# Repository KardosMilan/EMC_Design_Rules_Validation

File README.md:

# Automotive SEPIC Converter — EMC Design Rules Validation

> **Complete engineering workflow for an automotive-grade SEPIC DC-DC converter, from power-stage dimensioning through iterative EMC filter development to laboratory validation.**

---

## Overview

This project documents the full development and validation cycle of a switching power supply designed to meet demanding automotive EMC requirements. Starting from topology selection and component dimensioning, the work progresses through multiple hardware revisions, EMC-oriented filter design, and systematic laboratory validation — including electrical, frequency-domain, and thermal measurements.

Two contrasting PCB design iterations (SEPIC-A2 and SEPIC-B) are included side by side, demonstrating the measurable EMC impact of layout and filter decisions.

## Example of a designed PCB in aluminium housing

---

## Project Goals

- Design an automotive SEPIC converter power stage with appropriate switching-frequency selection and thermal management
- Identify and characterise conducted and radiated emission sources
- Develop and iteratively optimise LC input/output EMC filters
- Validate all design decisions through laboratory measurements
- Correlate theoretical calculations with experimental results
- Produce a documented engineering process suitable for future design iterations

---

## Engineering Workflow

### 1 — System Design
Component selection, power-stage dimensioning, switching-frequency optimisation, thermal considerations, and initial PCB layout preparation.

### 2 — EMC Filter Development
LC filter calculations, topology comparison, resonance analysis, and iterative optimisation verified against laboratory measurements. All calculation sheets are included in the repository.

### 3 — Prototype Manufacturing
Custom PCB design with microcontroller integration, automotive-grade components, and dedicated measurement interfaces. Two hardware revisions are provided:

| Revision     | Design Intent                                                        |
|---|---|
| **SEPIC-A2** | Reference iteration — poor EMC layout (emission source example)      |
| **SEPIC-B**  | Optimised iteration — improved EMC layout and filter (target design) |

### 4 — Measurement & Validation

| Domain      | Method                                                                               |
|---|---|
| Electrical  | Switching waveform analysis, frequency-domain characterisation, noise quantification |
| EMC         | Conducted emission measurement, filter effectiveness comparison between revisions    |
| Thermal     | FLIR thermal imaging, hotspot identification, thermal performance validation         |
| Correlation | Calculated vs. measured comparison across all key parameters                         |

---

## Repository Structure

```
EMC_Design_Rules_Validation/
├── 01_Documents/
│   ├── Filter design documentation
│   ├── Measurement plans
│   ├── Correlation calculations
│   ├── Thermal analysis results
│   └── Oscilloscope captures
│
├── 02_Pictures/
│   ├── Prototype photos
│   └── Laboratory setup
│
├── 03_Calculations/
│   ├── Design calculations
│   ├── EMC filter calculations
│   └── Validation worksheets
│
├── 04_SEPIC_microcontroller_prototype/
│   ├── Prototype hardware
│   ├── Embedded controller integration
│   └── Supporting component libraries
│
└── 05_HW_design/
    ├── SEPIC-A2/     ← bad EMC design example
    ├── SEPIC-B/      ← optimised EMC design example
    └── PCB design resources
```

---

## Technology Stack

| Area                   | Tools & Methods                         |
|---|---|
| PCB Design             | CAD schematic & layout tools            |
| Calculations           | Excel-based engineering worksheets      |
| Electrical Measurement | Oscilloscope (time & frequency domain)  |
| Thermal Measurement    | FLIR thermal camera                     |
| EMC Measurement        | Conducted emission laboratory equipment |
| Embedded Platform      | Automotive-grade microcontroller        |

---

## Key Outcomes

- Designed and validated two SEPIC converter hardware revisions with measurably different EMC behaviour
- Developed EMC filter solutions grounded in both analytical calculation and experimental iteration
- Demonstrated a systematic correlation methodology between design predictions and laboratory results
- Produced a complete, reproducible engineering workflow applicable to future power electronics and EMC projects

---

## Author

**Kardos Milan**  
Electrical / Electronics Engineer  
*Specialising in Power Electronics, EMC Validation, Hardware Design, and Embedded Systems*

---

## License

This repository is shared for portfolio and reference purposes. All rights reserved.

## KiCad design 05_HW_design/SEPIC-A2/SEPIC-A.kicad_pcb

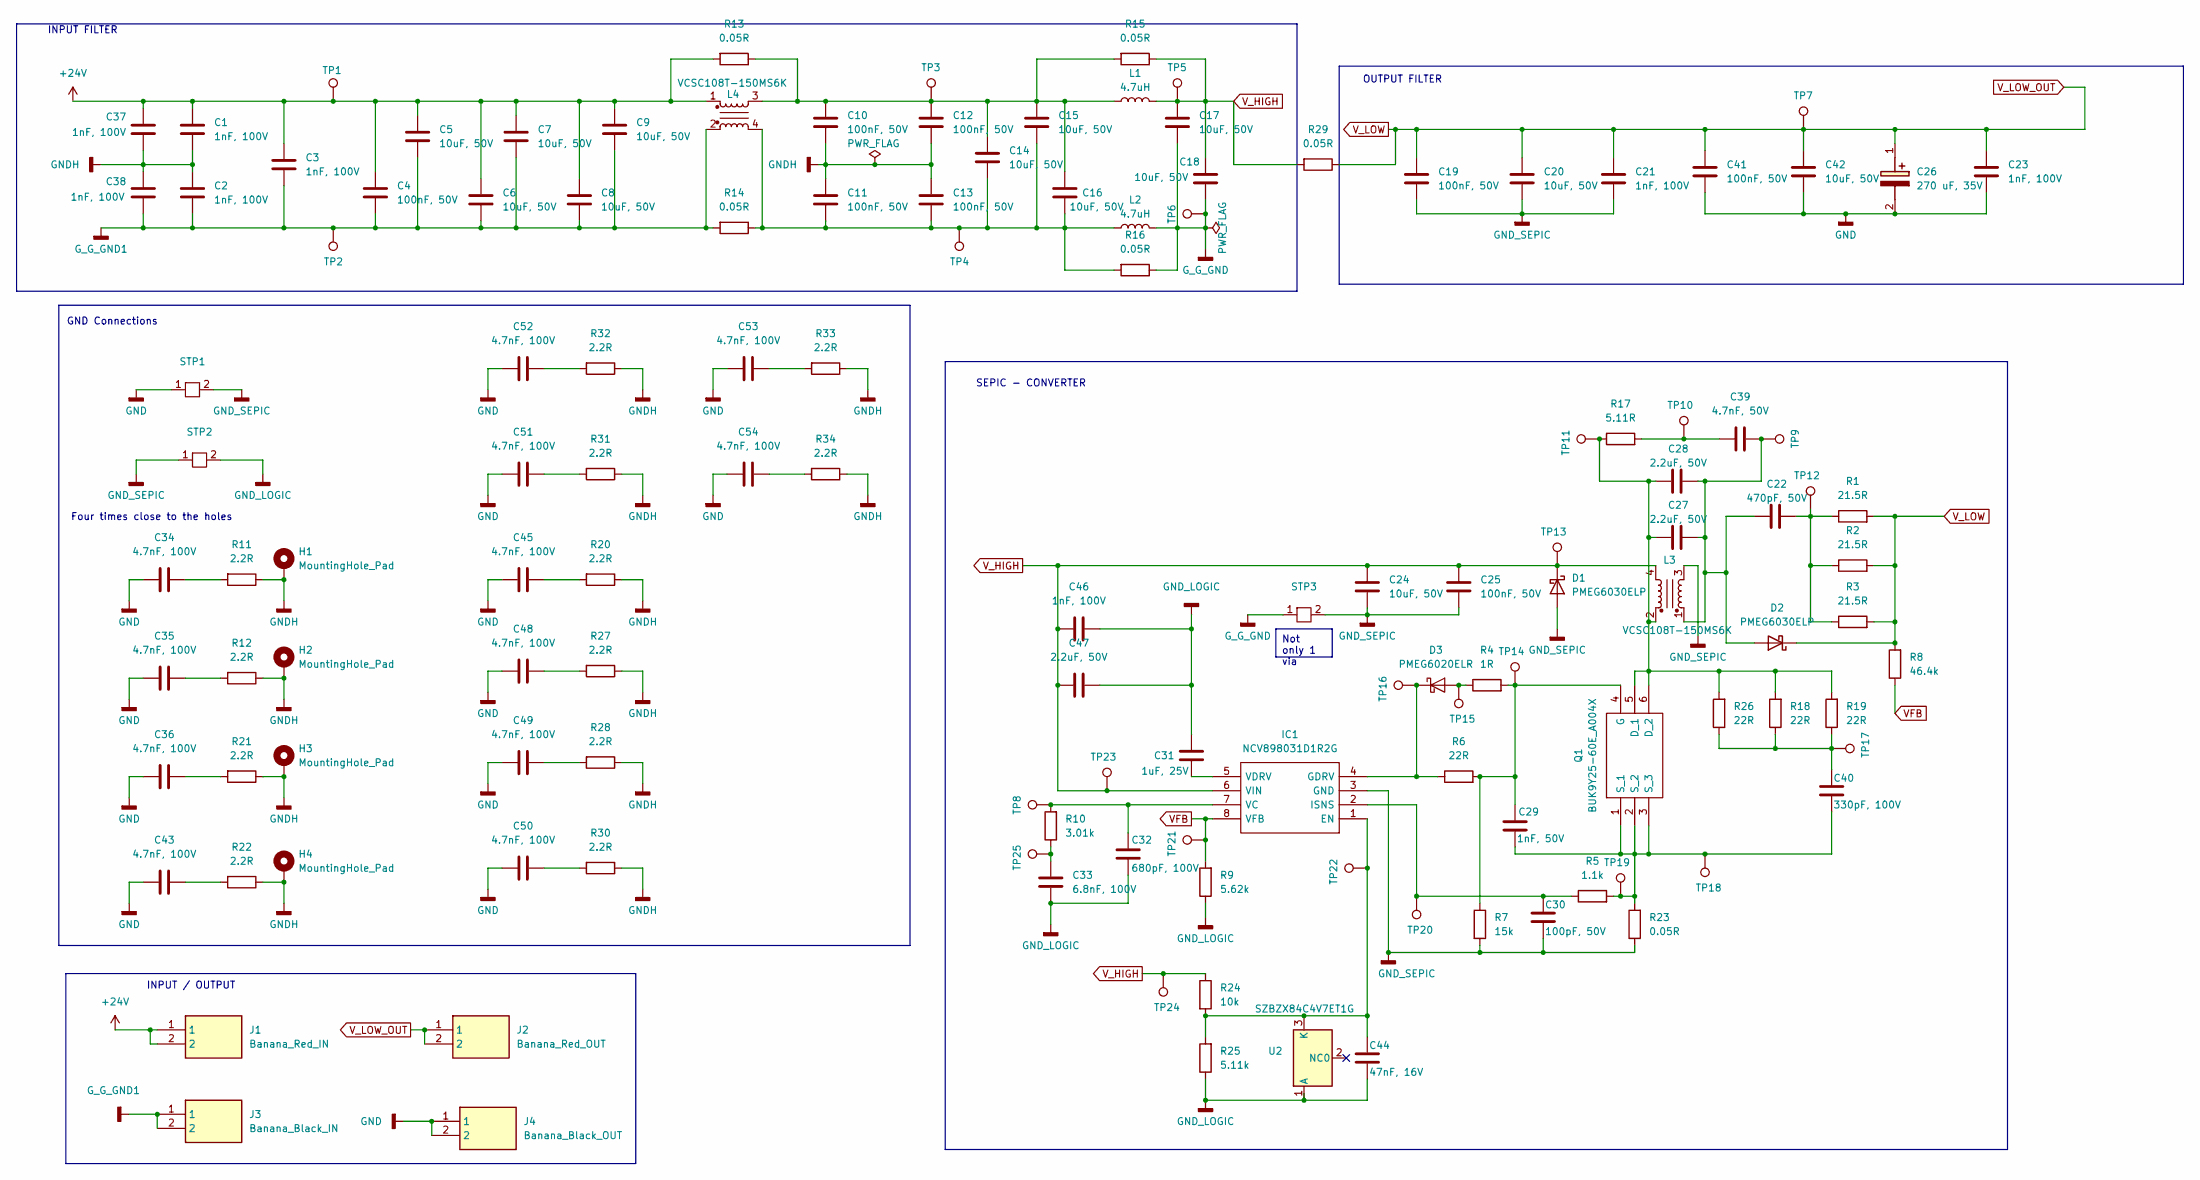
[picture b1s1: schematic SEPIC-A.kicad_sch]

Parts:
C1, C2, C3, C21, C23, C37, C38, C46: 1nF, 100V; C_0805_2012Metric_Pad1.18x1.45mm_HandSolder
C4, C10, C11, C12, C13, C19, C25, C41: 100nF, 50V; C_0805_2012Metric_Pad1.18x1.45mm_HandSolder
C5, C6, C7, C8, C9, C14, C15, C16, C17, C18, C20, C24, C42: 10uF, 50V; C_1210_3225Metric_Pad1.33x2.70mm_HandSolder
C22: 470pF, 50V; C_0603_1608Metric_Pad1.08x0.95mm_HandSolder
C26: 270 uF, 35V; CP_Elec_10x10.5; Manufacturer_Part_Number B40900B7277M000
C27, C28, C47: 2.2uF, 50V; C_1206_3216Metric_Pad1.33x1.80mm_HandSolder
C29: 1nF, 50V; C_0402_1005Metric
C30: 100pF, 50V; C_0402_1005Metric_Pad0.74x0.62mm_HandSolder
C31: 1uF, 25V; C_0805_2012Metric_Pad1.18x1.45mm_HandSolder
C32: 680pF, 100V; C_0603_1608Metric_Pad1.08x0.95mm_HandSolder
C33: 6.8nF, 100V; C_0603_1608Metric_Pad1.08x0.95mm_HandSolder
C34, C35, C36, C43, C45, C48, C49, C50, C51, C52, C53, C54: 4.7nF, 100V; C_0805_2012Metric_Pad1.18x1.45mm_HandSolder
C39: 4.7nF, 50V; C_1206_3216Metric_Pad1.33x1.80mm_HandSolder
C40: 330pF, 100V; C_0402_1005Metric_Pad0.74x0.62mm_HandSolder
C44: 47nF, 16V; C_0402_1005Metric_Pad0.74x0.62mm_HandSolder
D1, D2: PMEG6030ELP; D_SOD-128
D3: PMEG6020ELR; Nexperia_CFP3_SOD-123W
H1, H2, H3, H4: MountingHole_Pad; MountingHole_3.2mm_M3_Pad_Via
IC1: NCV898031D1R2G; SOIC127P600X175-8N; Manufacturer_Part_Number NCV898031D1R2G
J1: Banana_Red_IN; 242431; Manufacturer_Part_Number 24.243.1
J2: Banana_Red_OUT; 242431; Manufacturer_Part_Number 24.243.1
J3: Banana_Black_IN; 242432; Manufacturer_Part_Number 24.243.2
J4: Banana_Black_OUT; 242432; Manufacturer_Part_Number 24.243.2
L1, L2: 4.7uH; CLF6045__
L3, L4: VCSC108T-150MS6K; VCSC108T
Q1: BUK9Y25-60E_A004X; BUK9Y2560EA004X; Manufacturer_Part_Number BUK9Y25-60E/A004X
R1, R2, R3: 21.5R; R_0805_2012Metric_Pad1.20x1.40mm_HandSolder
R4: 1R; R_0805_2012Metric_Pad1.20x1.40mm_HandSolder
R5: 1.1k; R_0805_2012Metric_Pad1.20x1.40mm_HandSolder
R6, R18, R19, R26: 22R; R_0805_2012Metric_Pad1.20x1.40mm_HandSolder
R7: 15k; R_0402_1005Metric_Pad0.72x0.64mm_HandSolder
R8: 46.4k; R_0805_2012Metric_Pad1.20x1.40mm_HandSolder
R9: 5.62k; R_0402_1005Metric_Pad0.72x0.64mm_HandSolder
R10: 3.01k; R_0402_1005Metric_Pad0.72x0.64mm_HandSolder
R11, R12, R20, R21, R22, R27, R28, R30, R31, R32, R33, R34: 2.2R; R_0603_1608Metric_Pad0.98x0.95mm_HandSolder
R13, R14, R15, R16, R29: 0.05R; R_0805_2012Metric_Pad1.20x1.40mm_HandSolder
R17: 5.11R; C_0805_2012Metric_Pad1.18x1.45mm_HandSolder
R23: 0.05R; R_2512_6332Metric_Pad1.40x3.35mm_HandSolder
R24: 10k; R_0805_2012Metric_Pad1.20x1.40mm_HandSolder
R25: 5.11k; R_0805_2012Metric_Pad1.20x1.40mm_HandSolder
STP1, STP2, STP3: STP
TP1, TP2, TP3, TP4, TP5, TP6, TP7, TP8, TP9, TP10, TP11, TP12, TP13, TP14, TP15, TP16, TP17, TP18, TP19, TP20, TP21, TP22, TP23, TP24, TP25: TestPoint; TestPoint_Pad_D1.1mm
U2: SZBZX84C4V7ET1G; SOT-23

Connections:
+24V: C1.1, C3.1, C4.1, C5.1, C6.1, C7.1, C8.1, C9.1, C37.1, J1.1, J1.2, L4.1, R13.2, TP1.1
GND: C23.2, C26.2 (-), C34.1, C35.1, C36.1, C41.2, C42.2, C43.1, C45.1, C48.1, C49.1, C50.1, C51.1, C52.1, C53.1, C54.1, J4.1, J4.2, STP1.1
GNDH: C1.2, C2.1, C10.2, C11.1, C12.2, C13.1, C37.2, C38.1, H1.1, H2.1, H3.1, H4.1, R11.1, R12.1, R20.1, R21.1, R22.1, R27.1, R28.1, R30.1, R31.1, R32.1, R33.1, R34.1
GND_LOGIC: C31.1, C32.2, C33.2, C44.2, C46.2, C47.2, R9.1, R25.1, STP2.2, U2.1 (A)
GND_SEPIC: C19.2, C20.2, C21.2, C24.2, C25.2, C30.2, D1.2 (A), IC1.3 (GND), L3.3, R7.2, R23.1, STP1.2, STP2.1, STP3.2
G_G_GND: C17.2, C18.2, L2.2, R16.1, STP3.1, TP6.1
G_G_GND1: C2.2, C3.2, C4.2, C5.2, C6.2, C7.2, C8.2, C9.2, C38.2, J3.1, J3.2, L4.2, R14.2, TP2.1
unnamed: C10.1, C12.1, C14.1, C15.1, C16.1, L1.1, L4.3, R13.1, R15.2, TP3.1
unnamed: C11.2, C13.2, C14.2, C15.2, C16.2, L2.1, L4.4, R14.1, R16.2, TP4.1
unnamed: C22.2, R1.1, R2.1, R3.1, TP12.1
unnamed: C33.1, R10.1, TP25.1
unnamed: C34.2, R11.2
unnamed: C35.2, R12.2
unnamed: C36.2, R21.2
unnamed: C39.1, R17.2, TP10.1
unnamed: C40.1, R18.1, R19.1, R26.1, TP17.1
unnamed: C43.2, R22.2
unnamed: C45.2, R20.2
unnamed: C48.2, R27.2
unnamed: C49.2, R28.2
unnamed: C50.2, R30.2
unnamed: C51.2, R31.2
unnamed: C52.2, R32.2
unnamed: C53.2, R33.2
unnamed: C54.2, R34.2
unnamed: C22.1, C27.2, C28.2, C39.2, D2.2 (A), L3.1, TP9.1
unnamed: D3.2 (A), R4.1, TP15.1
unnamed: D3.1 (K), IC1.4 (GDRV), R6.1, TP16.1
unnamed: C44.1, IC1.1 (EN), R24.2, R25.2, TP22.1, U2.3 (K)
unnamed: C30.1, IC1.2 (ISNS), R5.1, TP20.1
unnamed: C32.1, IC1.7 (VC), R10.2, TP8.1
unnamed: C31.2, IC1.5 (VDRV)
unnamed: C27.1, C28.1, L3.2, Q1.5 (D_1), Q1.6 (D_2), R17.1, R18.2, R19.2, R26.2, TP11.1
unnamed: C29.1, Q1.4 (G), R4.2, R6.2, R7.1, TP14.1
unnamed: C29.2, C40.2, Q1.1 (S_1), Q1.2 (S_2), Q1.3 (S_3), R5.2, R23.2, TP18.1, TP19.1
VFB: IC1.8 (VFB), R8.1, R9.2, TP21.1
V_HIGH: C17.1, C18.1, C24.1, C25.1, C46.1, C47.1, D1.1 (K), IC1.6 (VIN), L1.2, L3.4, R15.1, R24.1, R29.2, TP5.1, TP13.1, TP23.1, TP24.1
V_LOW: C19.1, C20.1, C21.1, C23.1, C26.1 (+), C41.1, C42.1, D2.1 (K), J2.1, J2.2, R1.2, R2.2, R3.2, R8.2, R29.1, TP7.1

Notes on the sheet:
Not only 1 via
SEPIC - CONVERTER
GND Connections
INPUT FILTER
Four times close to the holes
INPUT / OUTPUT
OUTPUT FILTER

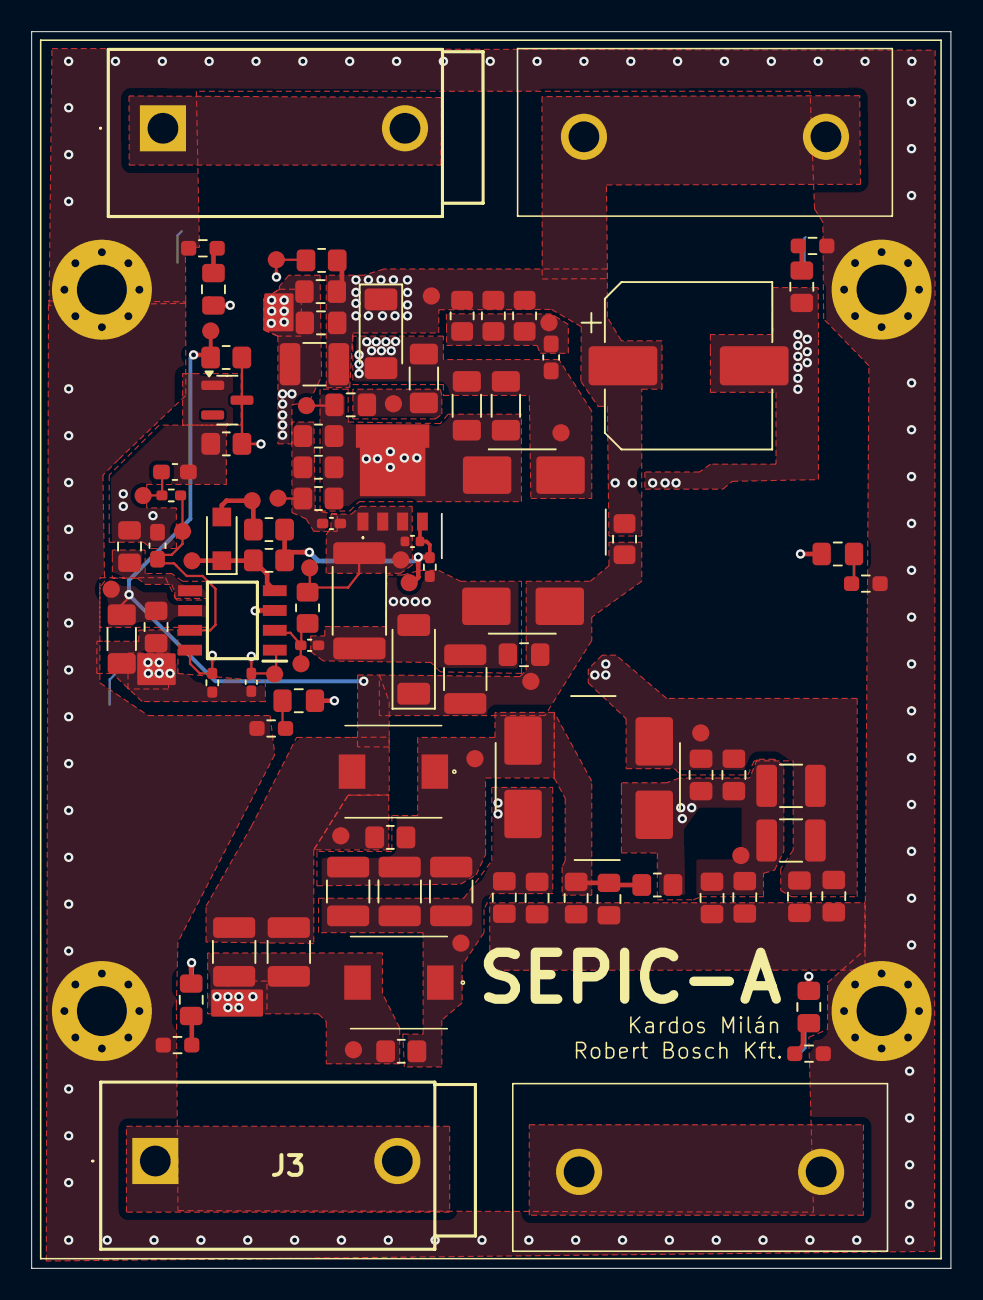
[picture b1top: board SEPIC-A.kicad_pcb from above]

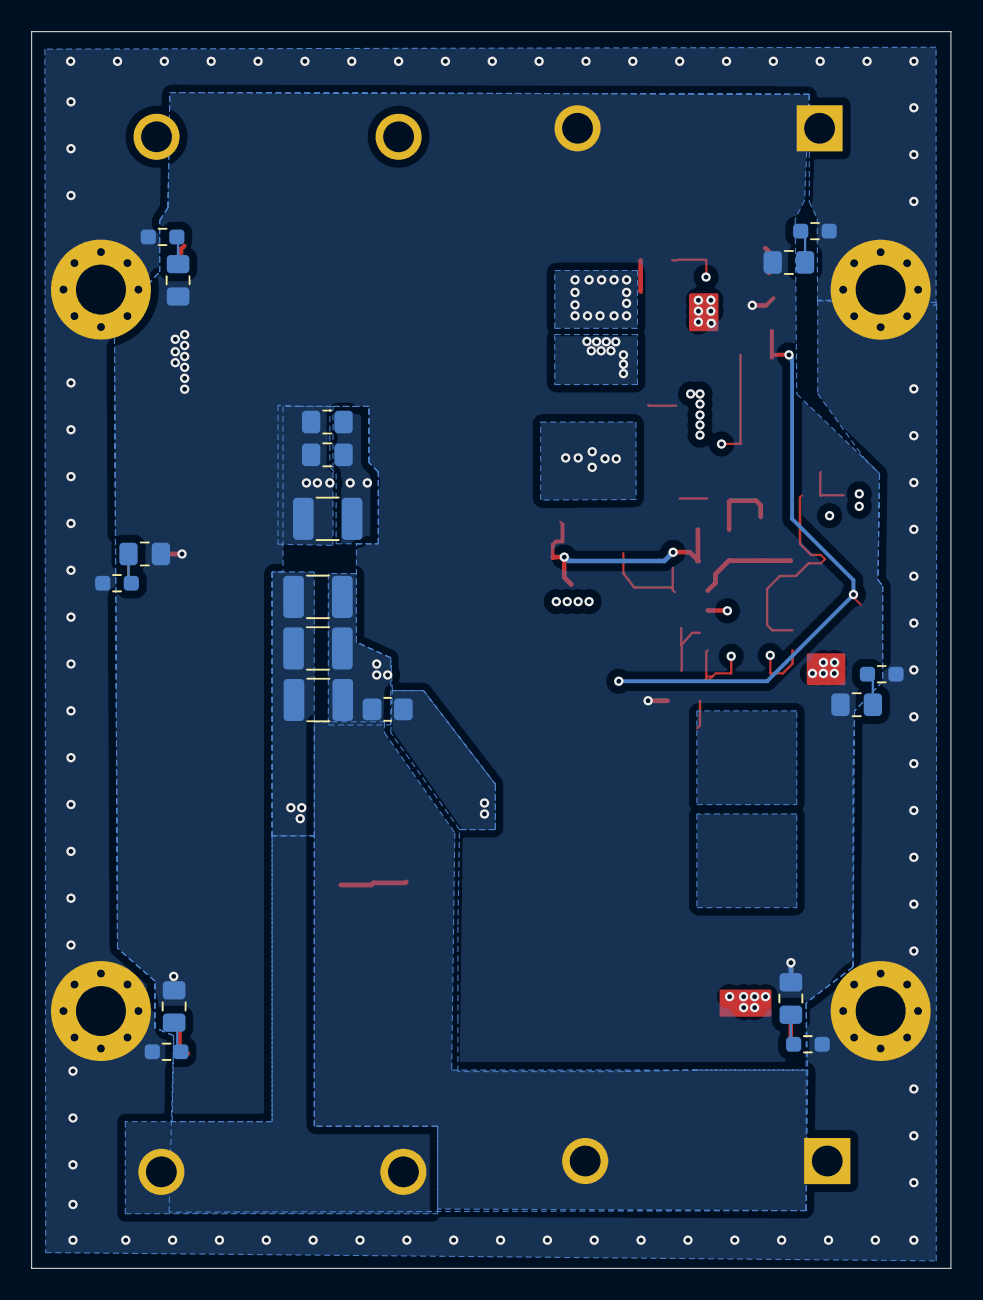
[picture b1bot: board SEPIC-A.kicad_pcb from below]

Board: 6 copper layers, 58.9 x 79.2 mm, 134 parts (19 on the bottom side), 38 nets.

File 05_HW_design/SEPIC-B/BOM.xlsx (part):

Reference | Value | Shop | Datasheet | Footprint | Qty | Bolti Darab | Ár (ft) | Összesen |  | 4db PCB-re [db] | Összesen [ft]
R5 | 1.1k | https://hu.farnell.com/panasonic/erj6geyj112v/res-1k1-5-0-12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 | http://industrial.panasonic.com/cdbs/www-data/pdf/RDA0000/AO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 | Resistor_SMD:R_0805_2012Metric_Pad1.20x1.40mm_HandSolder | 1 | 10 | 14.7 | 147 |  | 4 | 147
R4 | 1R | https://hu.farnell.com/bourns/cr0805-j-1r0elf/res-1r-5-0-125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 | https://www.farnell.com/datasheets/3693949.pdf | Resistor_SMD:R_0805_2012Metric_Pad1.20x1.40mm_HandSolder | 1 | 10 | 3.6 | 36 |  | 4 | 36
R28 | R | https://hu.farnell.com/walsin/wr12x151-jtl/res-150r-5-0-25w-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 | https://4donline.ihs.com/images/VipMasterIC/IC/WATC/WATC-S-A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 | Resistor_SMD:R_1206_3216Metric_Pad1.30x1.75mm_HandSolder | 1 | 10 | 5.5709999999999997 | 55.71 |  | 4 | 55.71
C31 | 1uF, 25V | https://hu.farnell.com/avx/08053g105zat2a/cap-1-f-25v-y5v-08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 | https://4donline.ihs.com/images/VipMasterIC/IC/AVXC/AVXC-S-A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 | Capacitor_SMD:C_0805_2012Metric_Pad1.18x1.45mm_HandSolder | 1 | 10 | 42.88 | 428.8 |  | 4 | 428.8
C32 | 680pF, 100V | https://hu.farnell.com/avx/06031c681kat2a/cap-680pf-100v-mlc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 | https://4donline.ihs.com/images/VipMasterIC/IC/AVXC/AVXC-S-A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 | Capacitor_SMD:C_0603_1608Metric_Pad1.08x0.95mm_HandSolder | 1 | 10 | 18 | 180 |  | 4 | 180
C5,C6,C7,C8,C9,C14,C15,C16,C17,C18,C20,C42 | 10uF, 50V | https://hu.farnell.com/tdk/cga6p3x7s1h106k250ab/cap-10-f-50v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 | https://www.farnell.com/datasheets/3816851.pdf | Capacitor_SMD:C_1210_3225Metric_Pad1.33x2.70mm_HandSolder | 12 | 12 | 244.47 | 2933.64 |  | 48 | 11734.56
C4,C10,C11,C12,C13,C19,C41 | 100nF, 50V | https://hu.farnell.com/kemet/c0805x104j5rac3316/cap-0-1-f-50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 | https://4donline.ihs.com/images/VipMasterIC/IC/KEME/KEME-S-A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 | Capacitor_SMD:C_0805_2012Metric_Pad1.18x1.45mm_HandSolder | 7 | 10 | 293 | 2930 |  | 28 | 8204
C1,C2,C3,C21,C23,C37,C38,C46 | 1nF, 100V | https://hu.farnell.com/kemet/c0805x102k1racauto/cap-1000pf-1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 | https://4donline.ihs.com/images/VipMasterIC/IC/KEME/KEME-S-A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 | Capacitor_SMD:C_0805_2012Metric_Pad1.18x1.45mm_HandSolder | 8 | 10 | 84 | 840 |  | 32 | 2688
C47 | 2.2uF, 50V | https://hu.farnell.com/kemet/c1206c225m5ractu/cap-2-2-f-50v-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 | https://search.kemet.com/component-documentation/download/sp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 | Capacitor_SMD:C_1206_3216Metric_Pad1.33x1.80mm_HandSolder | 1 | 10 | 89 | 890 |  | 4 | 890
C22 | 470pF, 50V | https://hu.farnell.com/kemet/c0603s471k5racauto/cap-mlcc-aec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 | https://4donline.ihs.com/images/VipMasterIC/IC/KEME/KEME-S-A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 | Capacitor_SMD:C_0603_1608Metric_Pad1.08x0.95mm_HandSolder | 1 | 10 | 75 | 750 |  | 4 | 750
C30 | 100pF, 50V | https://hu.farnell.com/kemet/c0402c101k5gacauto/cap-100pf-50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 | https://4donline.ihs.com/images/VipMasterIC/IC/KEME/KEME-S-A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 | Capacitor_SMD:C_0402_1005Metric_Pad0.74x0.62mm_HandSolder | 1 | 10 | 14 | 140 |  | 4 | 140
C29 | 1nF, 50V | https://hu.farnell.com/kemet/c0402c102j5racauto/cap-1000pf-5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 | https://4donline.ihs.com/images/VipMasterIC/IC/KEME/KEME-S-A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 | Capacitor_SMD:C_0402_1005Metric | 1 | 10 | 16 | 160 |  | 4 | 160
C34,C35,C36,C43 | 4.7nF, 100V | https://hu.farnell.com/kemet/c0805c472k1ractu/cap-4700pf-100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 | https://4donline.ihs.com/images/VipMasterIC/IC/KEME/KEME-S-A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 | Capacitor_SMD:C_0805_2012Metric_Pad1.18x1.45mm_HandSolder | 4 | 10 | 57 | 570 |  | 16 | 912
D1,D2 | PMEG6030ELP | https://hu.farnell.com/nexperia/pmeg6030elpx/schottky-rect-3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 | https://4donline.ihs.com/images/VipMasterIC/IC/NEXP/NEXP-S-A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 | Diode_SMD:D_SOD-128 | 2 | 5 | 192 | 960 |  | 8 | 1536
U2 | SZBZX84C4V7ET1G | https://hu.farnell.com/on-semiconductor/szbzx84c4v7et1g/zene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 | https://4donline.ihs.com/images/VipMasterIC/IC/ONSM/ONSM-S-A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 | Package_TO_SOT_SMD:SOT-23 | 1 | 5 | 98.5 | 492.5 |  | 4 | 492.5
R9 | 5.62k | https://hu.farnell.com/panasonic/erj2rkf5621x/res-5k62-1-0-1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 | https://4donline.ihs.com/images/VipMasterIC/IC/PANA/PANA-S-A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 | Resistor_SMD:R_0402_1005Metric_Pad0.72x0.64mm_HandSolder | 1 | 10 | 10.5 | 105 |  | 4 | 105
R6,R18,R19,R26 | 22R | https://hu.farnell.com/multicomp-pro/mp000064/res-aec-q200-2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 | https://4donline.ihs.com/images/VipMasterIC/IC/SCMP/SCMP-S-A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 | Resistor_SMD:R_0805_2012Metric_Pad1.20x1.40mm_HandSolder | 4 | 10 | 23.44 | 234.4 |  | 16 | 375.04
R23 | 0.05R | https://hu.farnell.com/multicomp-pro/mclrp12jtdrr050/res-det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 | https://4donline.ihs.com/images/VipMasterIC/IC/SCMP/SCMP-S-A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 | Resistor_SMD:R_2512_6332Metric_Pad1.40x3.35mm_HandSolder | 6 | 10 | 133.4 | 1334 |  | 24 | 3201.6
Q1 | BUK9Y25-60E_A004X | https://hu.farnell.com/nexperia/buk9y25-60e-115/mosfet-aecq1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 | https://assets.nexperia.com/documents/data-sheet/BUK9Y25-60E.pdf | KiCad1:BUK9Y2560EA004X | 1 | 1 | 345 | 345 |  | 4 | 1380
D3 | PMEG6020ELR | https://hu.farnell.com/nexperia/pmeg6020elrx/rectifier-schot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 | https://assets.nexperia.com/documents/data-sheet/PMEG6020ELR.pdf | Diode_SMD:Nexperia_CFP3_SOD-123W | 1 | 5 | 187.9 | 939.5 |  | 4 | 939.5
C26 | 270 uF, 35V | https://at.farnell.com/en-AT/epcos/b40900b7277m000/cap-270uf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 | https://product.tdk.com/system/files/dam/doc/product/capacit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 | Capacitor_SMD:CP_Elec_10x10.5 | 1 | Itthon nem elérhet? csak 1000 darabos |  |  | euroban lehet csak | 4
C40 | 330pF, 100V | https://hu.farnell.com/kemet/c0402c331j1gactu/cap-330pf-100v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 | https://search.kemet.com/component-documentation/download/sp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 | Capacitor_SMD:C_0402_1005Metric_Pad0.74x0.62mm_HandSolder | 1 | 10 | 29.3 | 293 |  | 4 | 293
C44 | 47nF, 16V | https://hu.farnell.com/yageo/cc0402krx7r7bb472/cap-4700pf-16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 | https://www.yageo.com/upload/media/product/productsearch/dat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 | Capacitor_SMD:C_0402_1005Metric_Pad0.74x0.62mm_HandSolder | 1 | 10 | 5.7 | 57 |  | 4 | 57
C25 | 100nF, 50V | https://hu.farnell.com/kemet/c0805x104j5rac3316/cap-0-1-f-50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 | https://search.kemet.com/component-documentation/download/sp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 | Capacitor_SMD:C_0805_2012Metric_Pad1.18x1.45mm_HandSolder | 1 | 10 | 293.3 | 2933 |  | 4 | 2933
C39 | 4.7nF, 50V | https://hu.farnell.com/kemet/c1206c475k5pactu/cap-4-7-f-50v-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 | https://search.kemet.com/component-documentation/download/sp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 | Capacitor_SMD:C_1206_3216Metric_Pad1.33x1.80mm_HandSolder | 1 | 10 | 85.3 | 853 |  | 4 | 853
L3,L4 | VCSC108T-150MS6K | https://www.digikey.de/de/products/detail/delta-electronics-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 | https://www.cyntec.com/upfile/products/download/(A8)%20VCSC1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 | Inductor_SMD:VCSC108T | 2 | 2 | 900 | 1800 | euroban lehet csak | 8
L1,L2 | 4.7uH | https://hu.farnell.com/tdk/clf6045t-4r7n-d/inductor-4-7uh-2-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 | https://www.farnell.com/datasheets/1763485.pdf | KiCad5:CLF6045__ | 2 | Ithon csak 1000 darabos |  |  |  | 8
R25 | 5.11k | https://hu.farnell.com/walsin/wr08x5111ftl/res-5k11-1-0-125w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 | https://4donline.ihs.com/images/VipMasterIC/IC/WATC/WATC-S-A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 | Resistor_SMD:R_0805_2012Metric_Pad1.20x1.40mm_HandSolder | 1 | 10 | 10 | 100 |  | 4 | 100
R11,R12,R21,R22 | 2.2R | https://hu.farnell.com/te-connectivity/crgcq0603j2r2/res-2r2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 | https://www.farnell.com/datasheets/2609223.pdf | Resistor_SMD:R_0201_0603Metric_Pad0.64x0.40mm_HandSolder | 4 | 10 | 5.17 | 51.7 |  | 16 | 82.72
R7 | 15k | https://hu.farnell.com/multicomp/mcmr04x153-jtl/res-15k-5-0-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 | https://www.farnell.com/datasheets/2860635.pdf | Resistor_SMD:R_0402_1005Metric_Pad0.72x0.64mm_HandSolder | 1 | 10 | 2.8 | 28 |  | 4 | 28
R8 | 46.4k | https://hu.farnell.com/multicomp-pro/mcwf08w4642btl/res-46k4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 | https://www.farnell.com/datasheets/2863884.pdf | Resistor_SMD:R_0805_2012Metric_Pad1.20x1.40mm_HandSolder | 1 | 10 | 121.4 | 1214 |  | 4 | 1214
J1 | Banana_Red_IN | https://hu.farnell.com/multicomp/24-243-1/banana-socket-20a-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 | https://www.farnell.com/datasheets/2963540.pdf | banana_red:242431 | 1 | 1 | 319 | 319 |  | 4 | 1276
J2 | Banana_Red_OUT | https://hu.farnell.com/multicomp/24-243-1/banana-socket-20a-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 | https://www.farnell.com/datasheets/2963540.pdf | banana_red:242431 | 1 | 1 | 319 | 319 |  | 4 | 1276
J3 | Banana_Black_IN | https://hu.farnell.com/multicomp/24-243-2/receptacle-20a-4mm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 | https://www.farnell.com/datasheets/2963540.pdf | banana_black:242432 | 1 | 1 | 319 | 319 |  | 4 | 1276
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
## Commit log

2026-06-19 initial commit: upload project
